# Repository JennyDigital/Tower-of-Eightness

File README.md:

# Tower-of-Eightness

Welcome to my play project of a homebrew computer based on the 6502 CPU used in many many home computers of the 80's.  This isn't meant to be a guide to how you should build a 6502 based computer but it is meant to be fun and it does work.  I had never done one before so there's lots to improve upon I'm sure and I would love to hear of any exploits or builds similar to or the same as mine.

P.S.  I am planning to bring BBC BASIC to this system as it's sooooo good.

P.P.S.  I will be continuing to develop this machine for some time especially over weekends.

Have Fun!

*JenniferDigital.*

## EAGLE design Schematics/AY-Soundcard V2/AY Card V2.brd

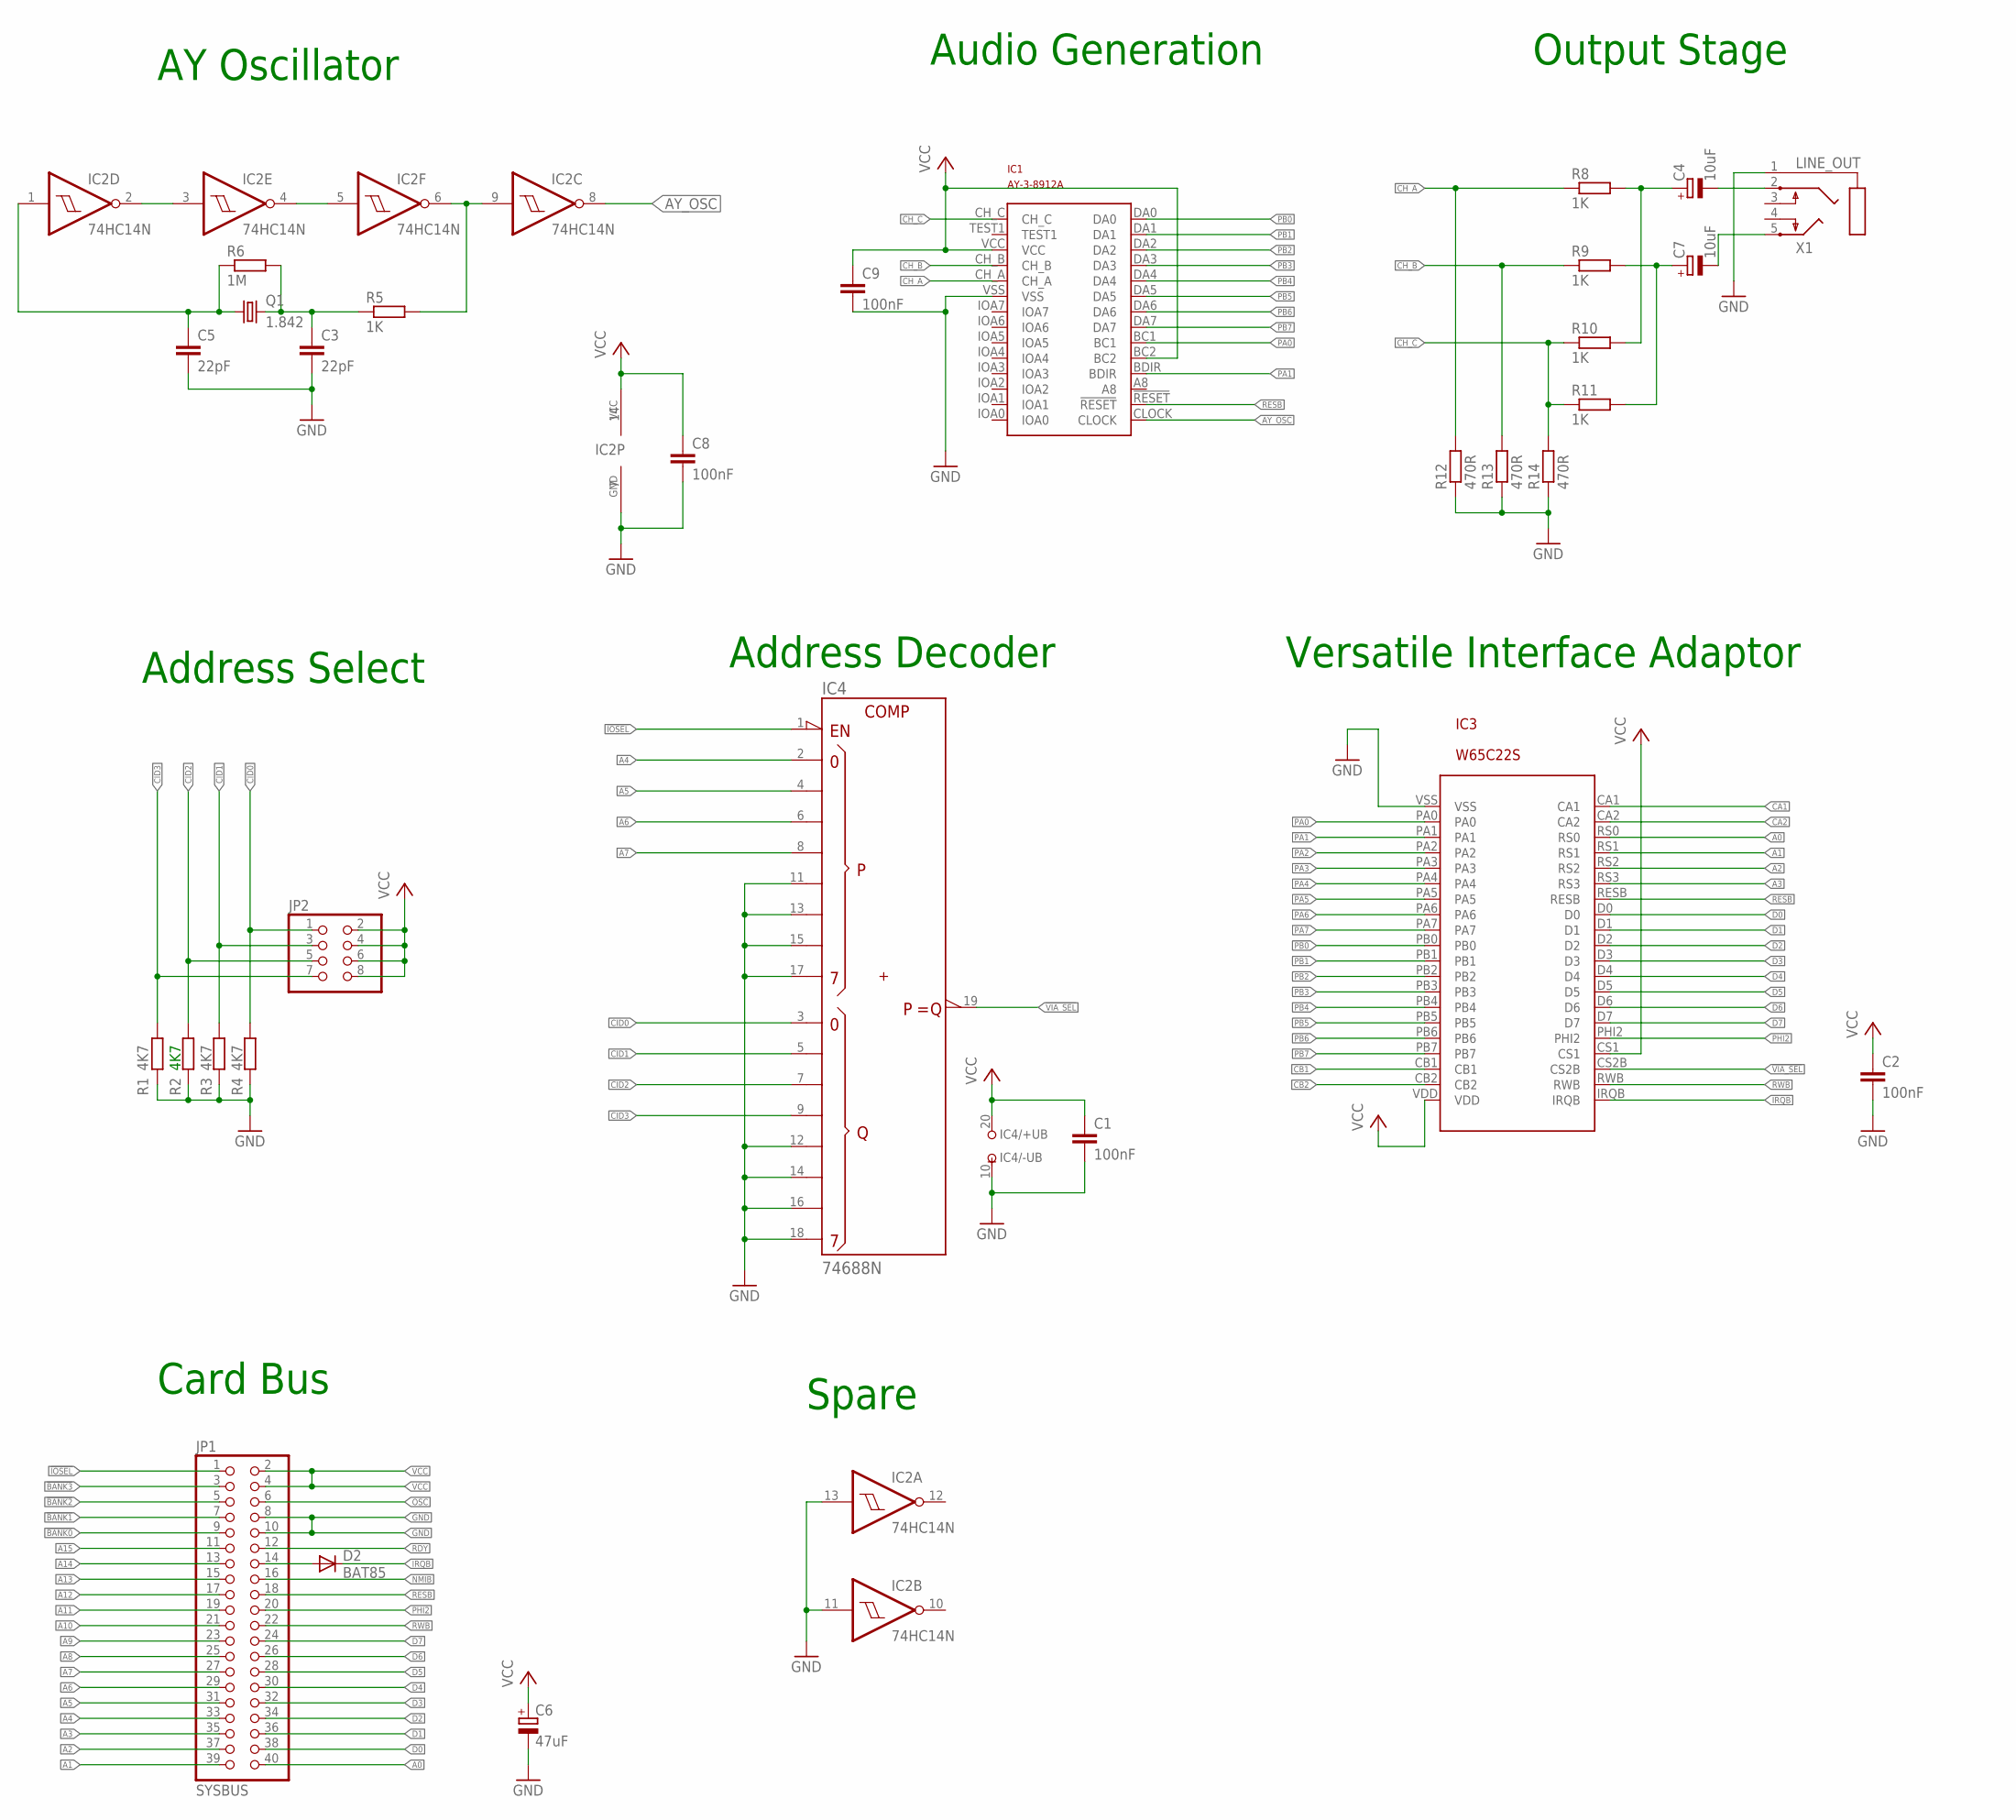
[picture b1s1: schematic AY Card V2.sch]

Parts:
C1, C2, C8, C9: 100nF; C050-025X075
C3, C5: 22pF; C050-025X075
C4, C7: 10uF; E2-5
C6: 47uF; E2,5-7
D2: BAT85; DO34-7
IC1: AY-3-8912A; DIP
IC2: 74HC14N; DIL14
IC3: W65C22S; W65C22-DIP
IC4: 74688N; DIL20
JP1: SYSBUS; 2X20/90
JP2: PINHD-2X4; 2X04
Q1: 1.842; HC49/S
R1, R2, R3, R4: 4K7; 0207/10
R5, R8, R9, R10, R11: 1K; 0207/2V
R6: 1M; 0207/2V
R12: 470R; 0207/2V
R13, R14: 470R; 0207/10
X1: LINE_OUT; STX3100

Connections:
!BANK0: JP1.9
!BANK1: JP1.7
!BANK2: JP1.5
!BANK3: JP1.3
!IOSEL: IC4.1 (!G), JP1.1
!VIA_SEL: IC3.CS2B, IC4.19 (!P=Q)
A0: IC3.RS0, JP1.40
A1: IC3.RS1, JP1.39
A2: IC3.RS2, JP1.37
A3: IC3.RS3, JP1.35
A4: IC4.2 (P0), JP1.33
A5: IC4.4 (P1), JP1.31
A6: IC4.6 (P2), JP1.29
A7: IC4.8 (P3), JP1.27
A8: JP1.25
A9: JP1.23
A10: JP1.21
A11: JP1.19
A12: JP1.17
A13: JP1.15
A14: JP1.13
A15: JP1.11
AY_OSC: IC1.CLOCK, IC2.8 (O)
CA1: IC3.CA1
CA2: IC3.CA2
CB1: IC3.CB1
CB2: IC3.CB2
CH_A: IC1.CH_A, R8.1, R12.2
CH_B: IC1.CH_B, R9.1, R13.2
CH_C: IC1.CH_C, R10.1, R11.1, R14.2
CID0: IC4.3 (Q0), JP2.1, R4.2
CID1: IC4.5 (Q1), JP2.3, R3.2
CID2: IC4.7 (Q2), JP2.5, R2.2
CID3: IC4.9 (Q3), JP2.7, R1.2
D0: IC3.D0, JP1.38
D1: IC3.D1, JP1.36
D2: IC3.D2, JP1.34
D3: IC3.D3, JP1.32
D4: IC3.D4, JP1.30
D5: IC3.D5, JP1.28
D6: IC3.D6, JP1.26
D7: IC3.D7, JP1.24
GND: C1.2, C2.2, C3.2, C5.2, C6.-, C8.2, C9.2, IC1.VSS, IC2.7 (GND), IC2.11 (I), IC2.13 (I), IC3.VSS, IC4.10 (-UB), IC4.11 (P4), IC4.12 (Q4), IC4.13 (P5), IC4.14 (Q5), IC4.15 (P6), IC4.16 (Q6), IC4.17 (P7), IC4.18 (Q7), JP1.8, JP1.10, R1.1, R2.1, R3.1, R4.1, R12.1, R13.1, R14.1, X1.1
IRQB: D2.C, IC3.IRQB
unnamed: D2.A, JP1.14
unnamed: C4.+, R8.2, R10.2
unnamed: C7.+, R9.2, R11.2
unnamed: C7.-, X1.5
unnamed: C4.-, X1.2
unnamed: IC2.4 (O), IC2.5 (I)
unnamed: IC2.6 (O), IC2.9 (I), R5.2
unnamed: C3.1, Q1.2, R5.1, R6.2
unnamed: C5.1, IC2.1 (I), Q1.1, R6.1
unnamed: IC2.2 (O), IC2.3 (I)
NMIB: JP1.16
OSC: JP1.6
PA0: IC1.BC1, IC3.PA0
PA1: IC1.BDIR, IC3.PA1
PA2: IC3.PA2
PA3: IC3.PA3
PA4: IC3.PA4
PA5: IC3.PA5
PA6: IC3.PA6
PA7: IC3.PA7
PB0: IC1.DA0, IC3.PB0
PB1: IC1.DA1, IC3.PB1
PB2: IC1.DA2, IC3.PB2
PB3: IC1.DA3, IC3.PB3
PB4: IC1.DA4, IC3.PB4
PB5: IC1.DA5, IC3.PB5
PB6: IC1.DA6, IC3.PB6
PB7: IC1.DA7, IC3.PB7
PHI2: IC3.PHI2, JP1.20
RDY: JP1.12
RESB: IC1.!RESET, IC3.RESB, JP1.18
RWB: IC3.RWB, JP1.22
VCC: C1.1, C2.1, C6.+, C8.1, C9.1, IC1.BC2, IC1.VCC, IC2.14 (VCC), IC3.CS1, IC3.VDD, IC4.20 (+UB), JP1.2, JP1.4, JP2.2, JP2.4, JP2.6, JP2.8

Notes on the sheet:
Card Bus
Address Select
Address Decoder
Versatile Interface Adaptor
Audio Generation
Output Stage
AY Oscillator
Spare

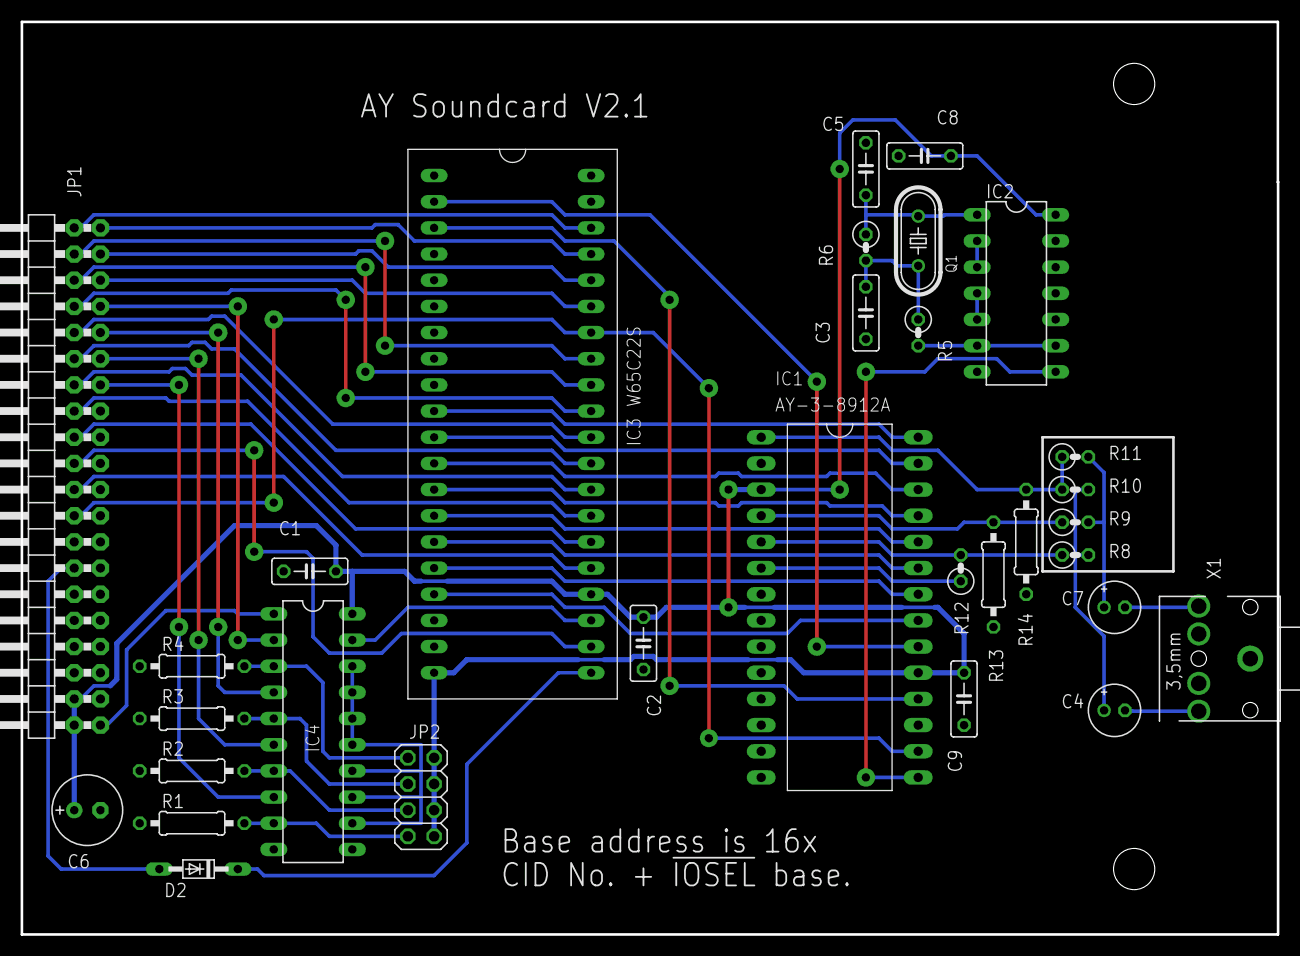
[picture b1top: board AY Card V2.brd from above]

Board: 2 copper layers, 121.9 x 88.6 mm, 31 parts (0 on the bottom side), 52 nets.

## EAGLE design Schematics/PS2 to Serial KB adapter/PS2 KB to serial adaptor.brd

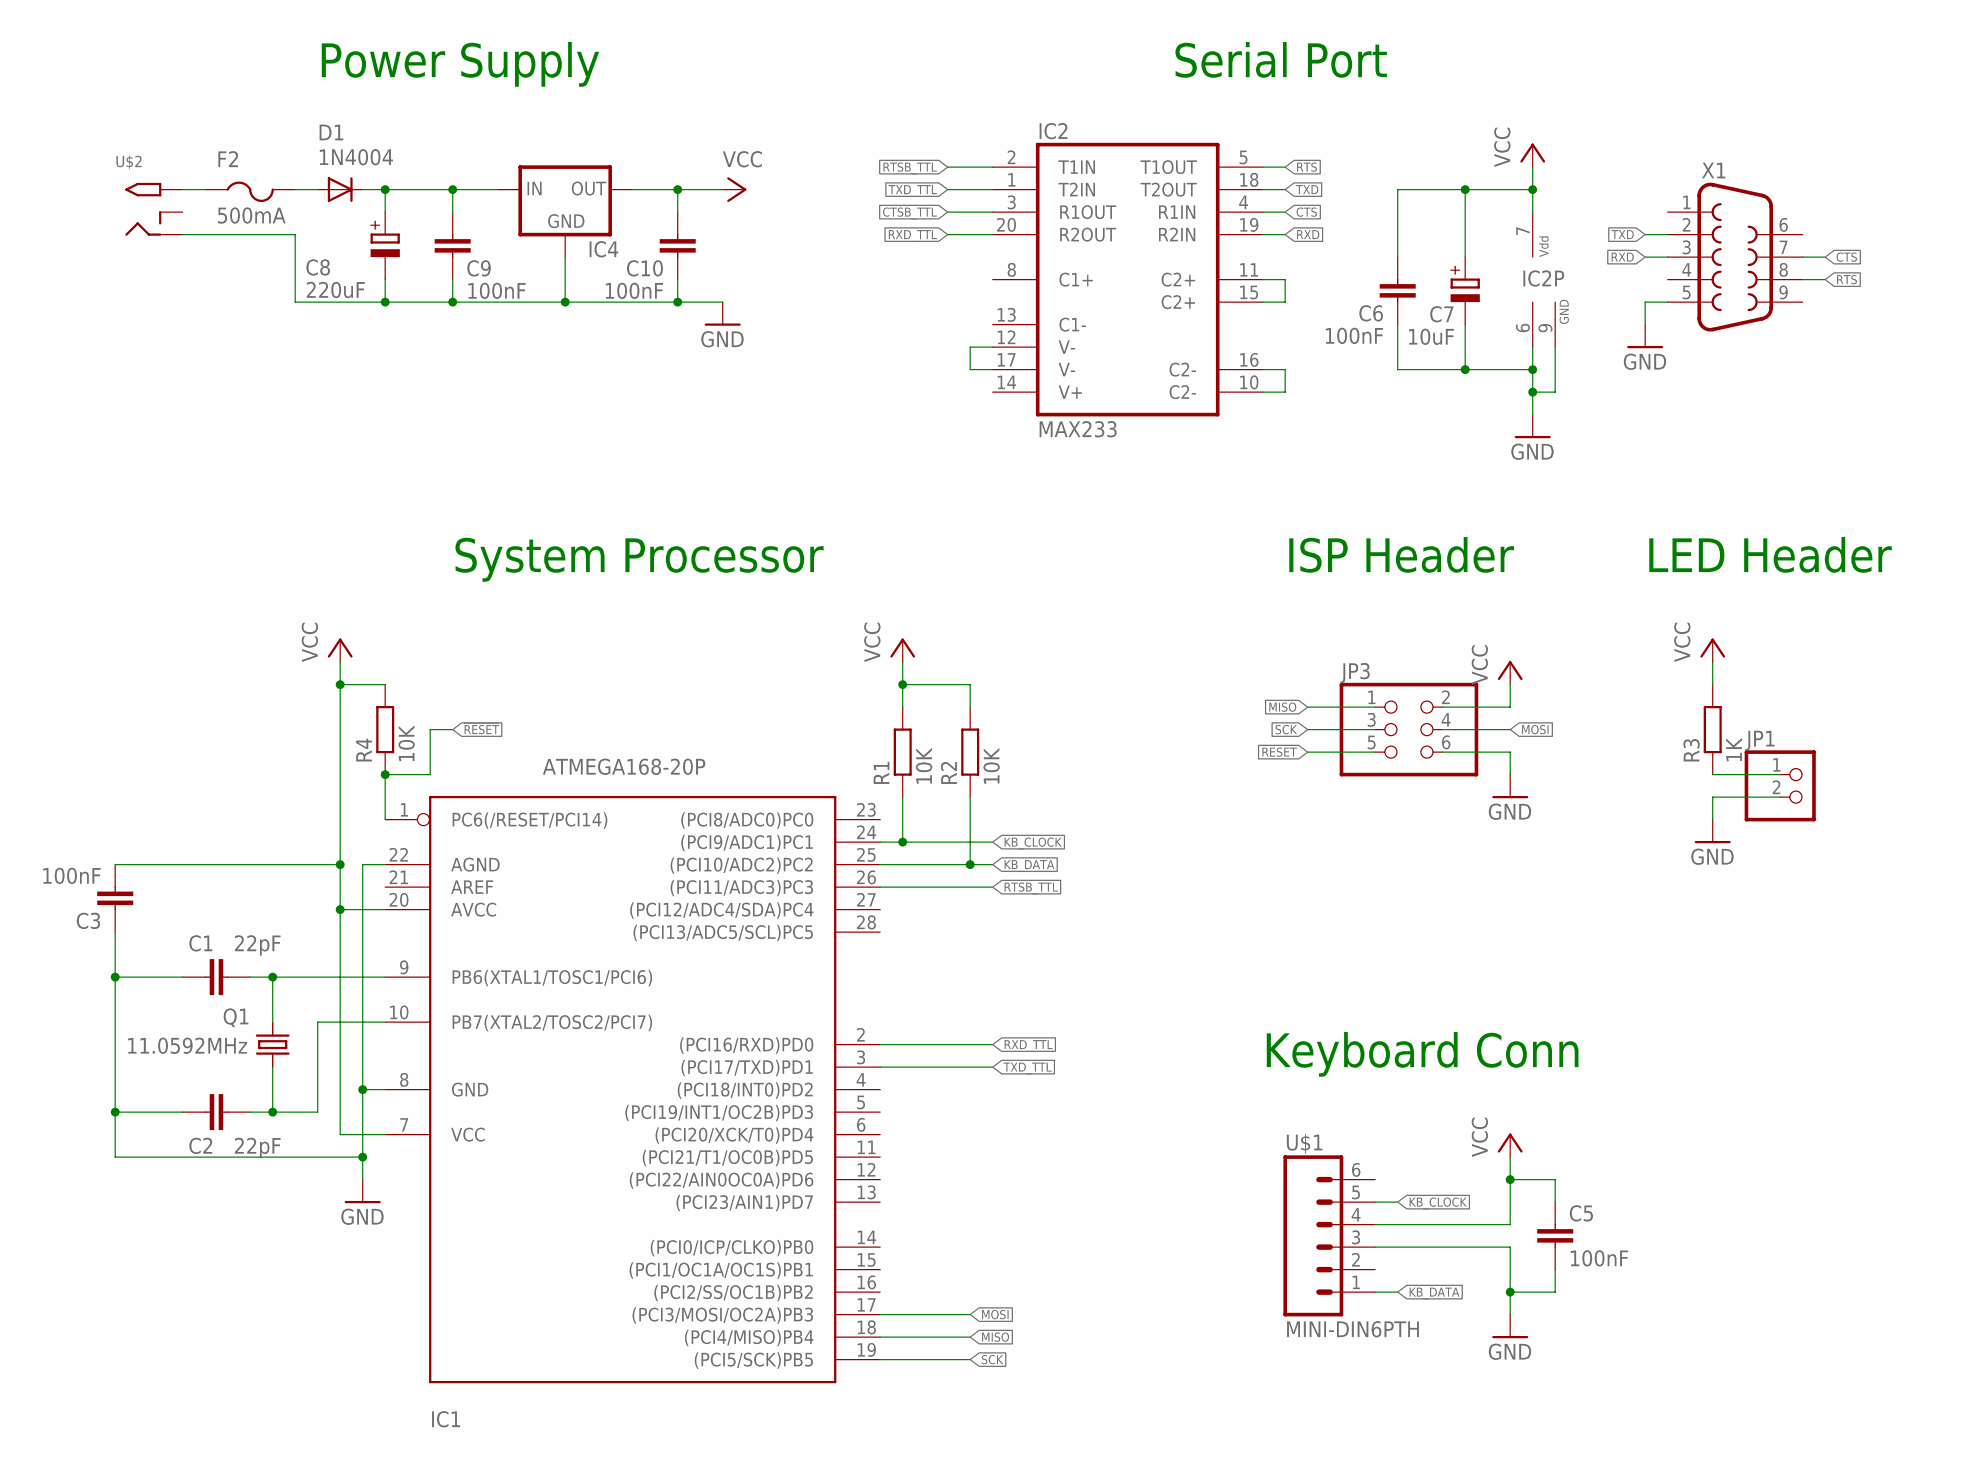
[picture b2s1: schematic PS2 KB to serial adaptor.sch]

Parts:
C1, C2: 22pF; C025-024X044
C3, C6, C9, C10: 100nF; C025-024X044
C5: 100nF; C050-024X044
C7: 10uF; E2,5-5
C8: 220uF; E2,5-7
D1: 1N4004; DO41-10
F2: 500mA; 1812
IC1: ATMEGA168-20P; DIL28-3
IC2: MAX233; DIL20
IC4: 78XXL
JP1: PINHD-1X2; 1X02
JP3: PINHD-2X3; 2X03
Q1: 11.0592MHz; HC49U-V
R1, R2: 10K; 0207/2V
R3: 1K; 0207/2V
R4: 10K; 0207/7
U$1: MINI-DIN6PTH; MINI-DIN6
U$2: 2.1MMJACKTHM; PJ-102A
X1: F09HP

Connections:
!RESET: IC1.1 (PC6(/RESET/PCI14)), JP3.5, R4.1
CTS: IC2.4 (R1IN), X1.7
CTSB_TTL: IC2.3 (R1OUT)
GND: C1.1, C2.1, C3.1, C5.1, C6.1, C7.-, C8.-, C9.1, C10.1, IC1.8 (GND), IC1.22 (AGND), IC2.6 (GND), IC2.9 (GND), IC4.GND, JP1.2, JP3.6, U$1.3, U$2.RING, X1.5
KB_CLOCK: IC1.24 ((PCI9/ADC1)PC1), R1.1, U$1.5
KB_DATA: IC1.25 ((PCI10/ADC2)PC2), R2.1, U$1.1
MISO: IC1.18 ((PCI4/MISO)PB4), JP3.1
MOSI: IC1.17 ((PCI3/MOSI/OC2A)PB3), JP3.4
unnamed: IC2.12 (V-), IC2.17 (V-)
unnamed: IC2.11 (C2+), IC2.15 (C2+)
unnamed: IC2.10 (C2-), IC2.16 (C2-)
unnamed: C8.+, C9.2, D1.C, IC4.IN
unnamed: JP1.1, R3.1
unnamed: D1.A, F2.2
unnamed: C1.2, IC1.9 (PB6(XTAL1/TOSC1/PCI6)), Q1.2
unnamed: C2.2, IC1.10 (PB7(XTAL2/TOSC2/PCI7)), Q1.1
unnamed: F2.1, U$2.TIP
RTS: IC2.5 (T1OUT), X1.8
RTSB_TTL: IC1.26 ((PCI11/ADC3)PC3), IC2.2 (T1IN)
RXD: IC2.19 (R2IN), X1.3
RXD_TTL: IC1.2 ((PCI16/RXD)PD0), IC2.20 (R2OUT)
SCK: IC1.19 ((PCI5/SCK)PB5), JP3.3
TXD: IC2.18 (T2OUT), X1.2
TXD_TTL: IC1.3 ((PCI17/TXD)PD1), IC2.1 (T2IN)
VCC: C3.2, C5.2, C6.2, C7.+, C10.2, IC1.7 (VCC), IC1.20 (AVCC), IC2.7 (VDD), IC4.OUT, JP3.2, R1.2, R2.2, R3.2, R4.2, U$1.4

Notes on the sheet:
Power Supply
Keyboard Conn
Serial Port
System Processor
ISP Header
LED Header

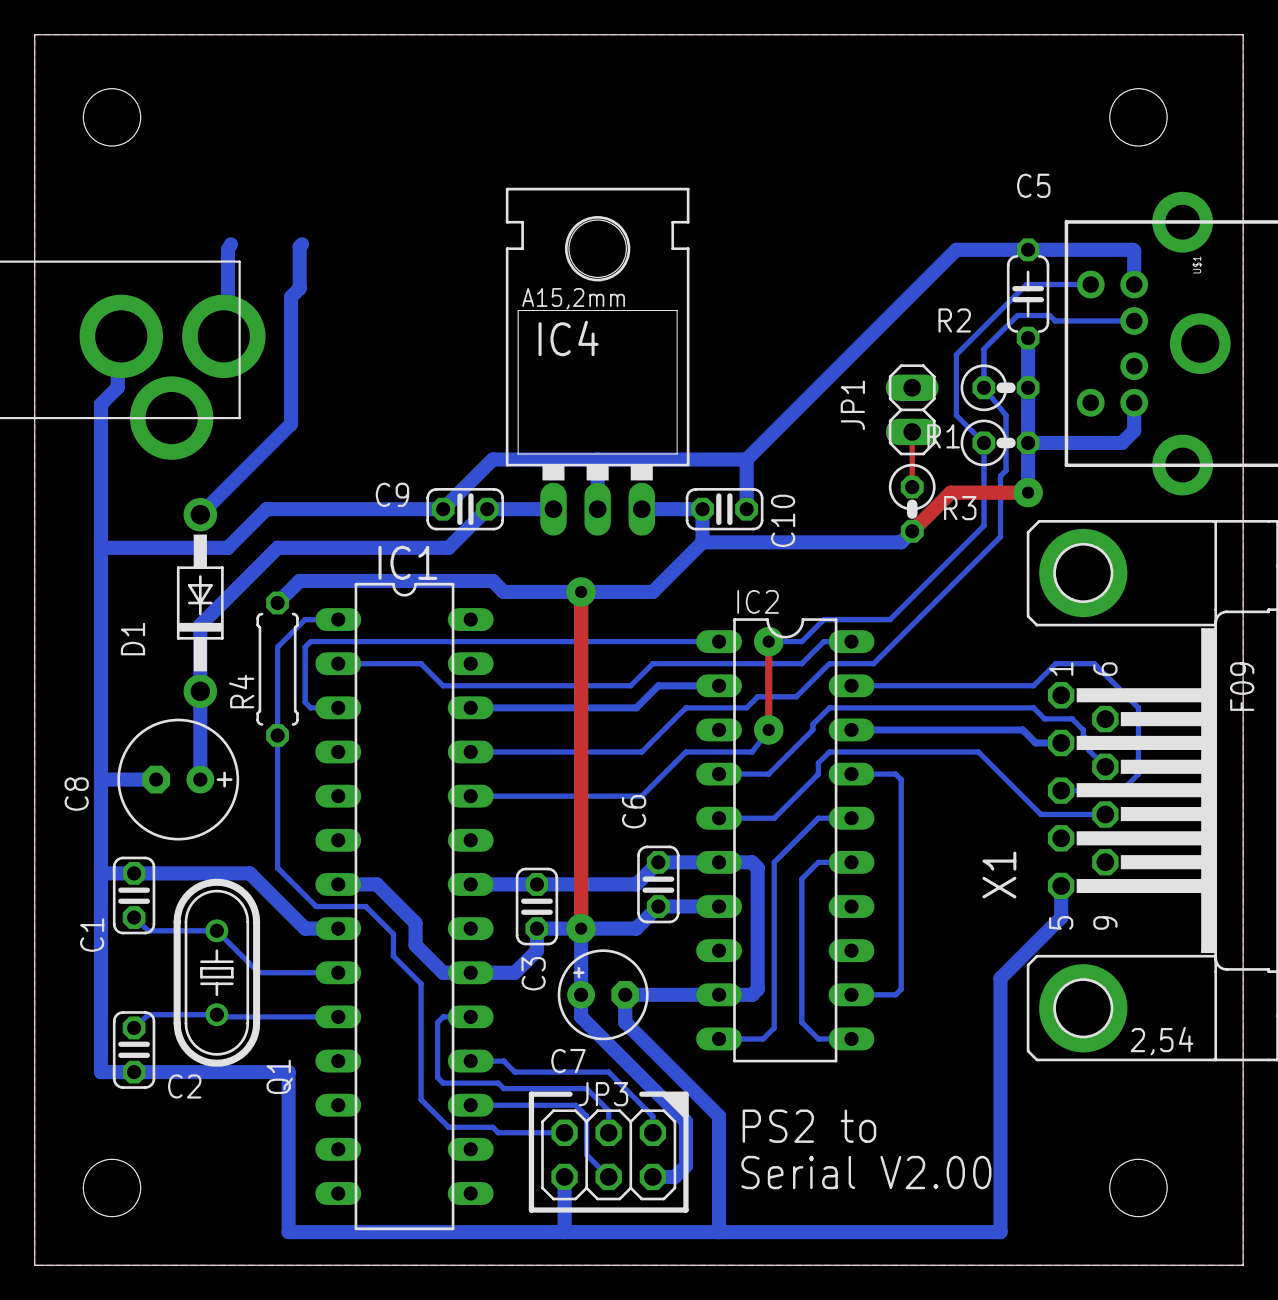
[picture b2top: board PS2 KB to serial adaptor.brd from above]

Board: 2 copper layers, 69.5 x 70.8 mm, 24 parts (1 on the bottom side), 24 nets.

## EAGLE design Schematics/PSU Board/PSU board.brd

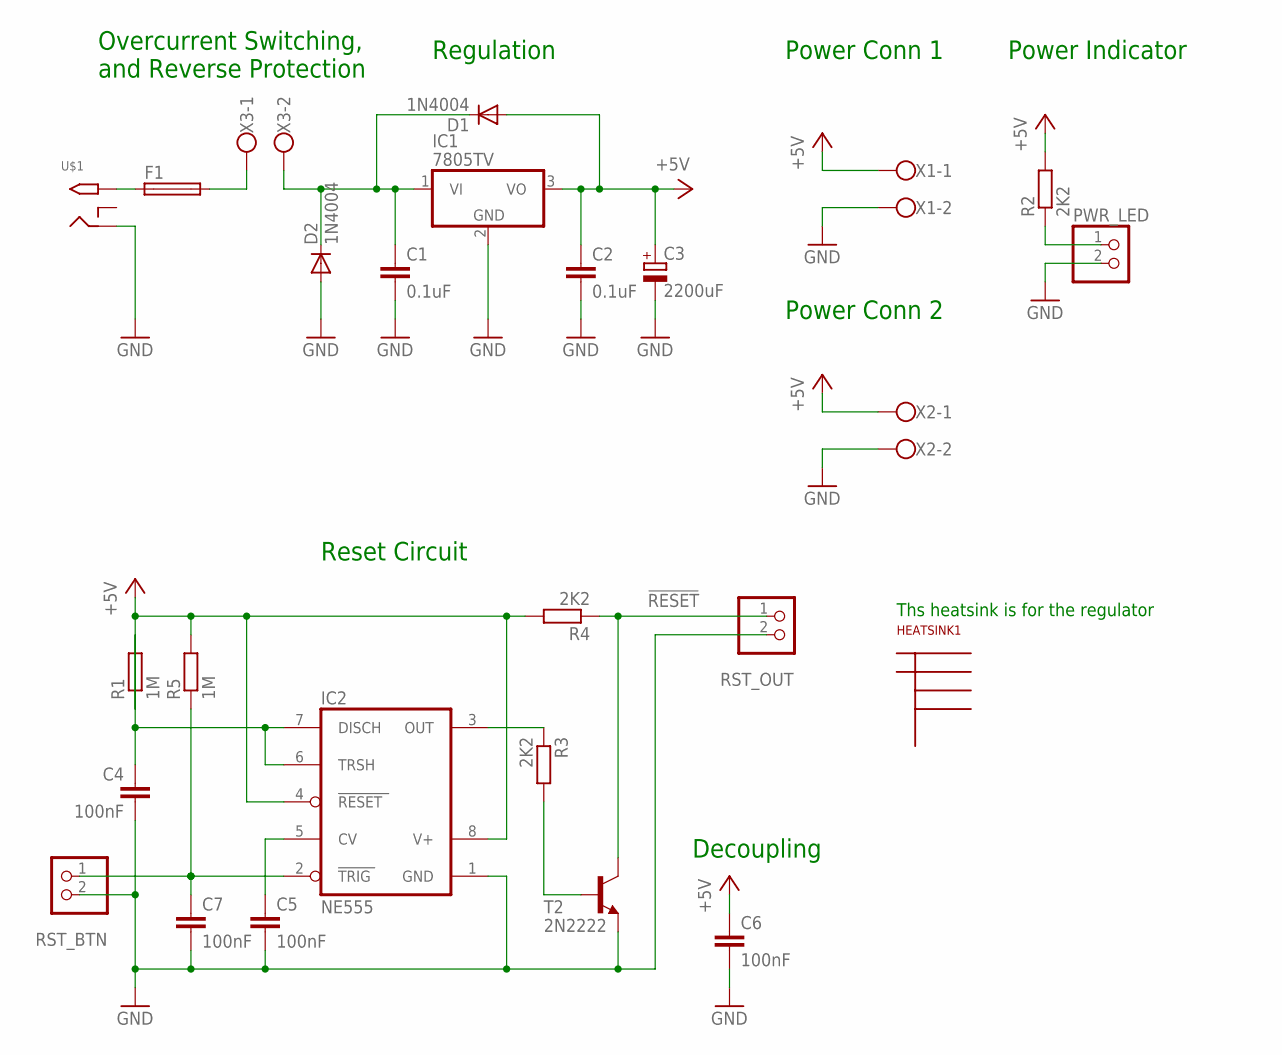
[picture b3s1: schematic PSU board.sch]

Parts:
C1, C2: 0.1uF; C025-025X050
C3: 2200uF; E7,5-18
C4, C5, C6, C7: 100nF; C025-025X050
D1, D2: 1N4004; DO41-10
F1: SH22,5A
HEATSINK1: FISCHER-50_HSINK; FISHER-50
IC1: 7805TV; TO220V
IC2: NE555; DIL08
PWR_LED: PINHD-1X2; 1X02
R1: 1M; 0207/2V
R2: 2K2; 0207/10
R3, R4: 2K2; 0207/2V
R5: 1M; 0207/10
RST_BTN: PINHD-1X2; 1X02
RST_OUT: PINHD-1X2; 1X02
T2: 2N2222; TO18
U$1: 2.1MMJACKTHM; PJ-102A
X1, X2, X3: W237-102

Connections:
!RESET: R4.1, RST_OUT.1, T2.3 (C)
+5V: C2.1, C3.+, C6.1, D1.A, IC1.3 (VO), IC2.4 (RESET), IC2.8 (V+), R1.1, R2.2, R4.2, R5.2, X1.1, X2.1
+V_IN: C1.1, D1.C, D2.C, IC1.1 (VI), X3.2
GND: C1.2, C2.2, C3.-, C4.2, C5.2, C6.2, C7.2, D2.A, IC1.2 (GND), IC2.1 (GND), PWR_LED.2, RST_BTN.2, RST_OUT.2, T2.1 (E), U$1.RING, X1.2, X2.2
unnamed: PWR_LED.1, R2.1
unnamed: F1.2, X3.1
unnamed: F1.1, U$1.TIP
unnamed: C4.1, IC2.6 (TRSH), IC2.7 (DISCH), R1.2
unnamed: C5.1, IC2.5 (CV)
unnamed: C7.1, IC2.2 (TRIG), R5.1, RST_BTN.1
unnamed: R3.2, T2.2 (B)
unnamed: IC2.3 (OUT), R3.1

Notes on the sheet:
Decoupling
Regulation
Overcurrent Switching, and Reverse Protection
Power Indicator
Reset Circuit
Power Conn 1
Power Conn 2
Ths heatsink is for the regulator

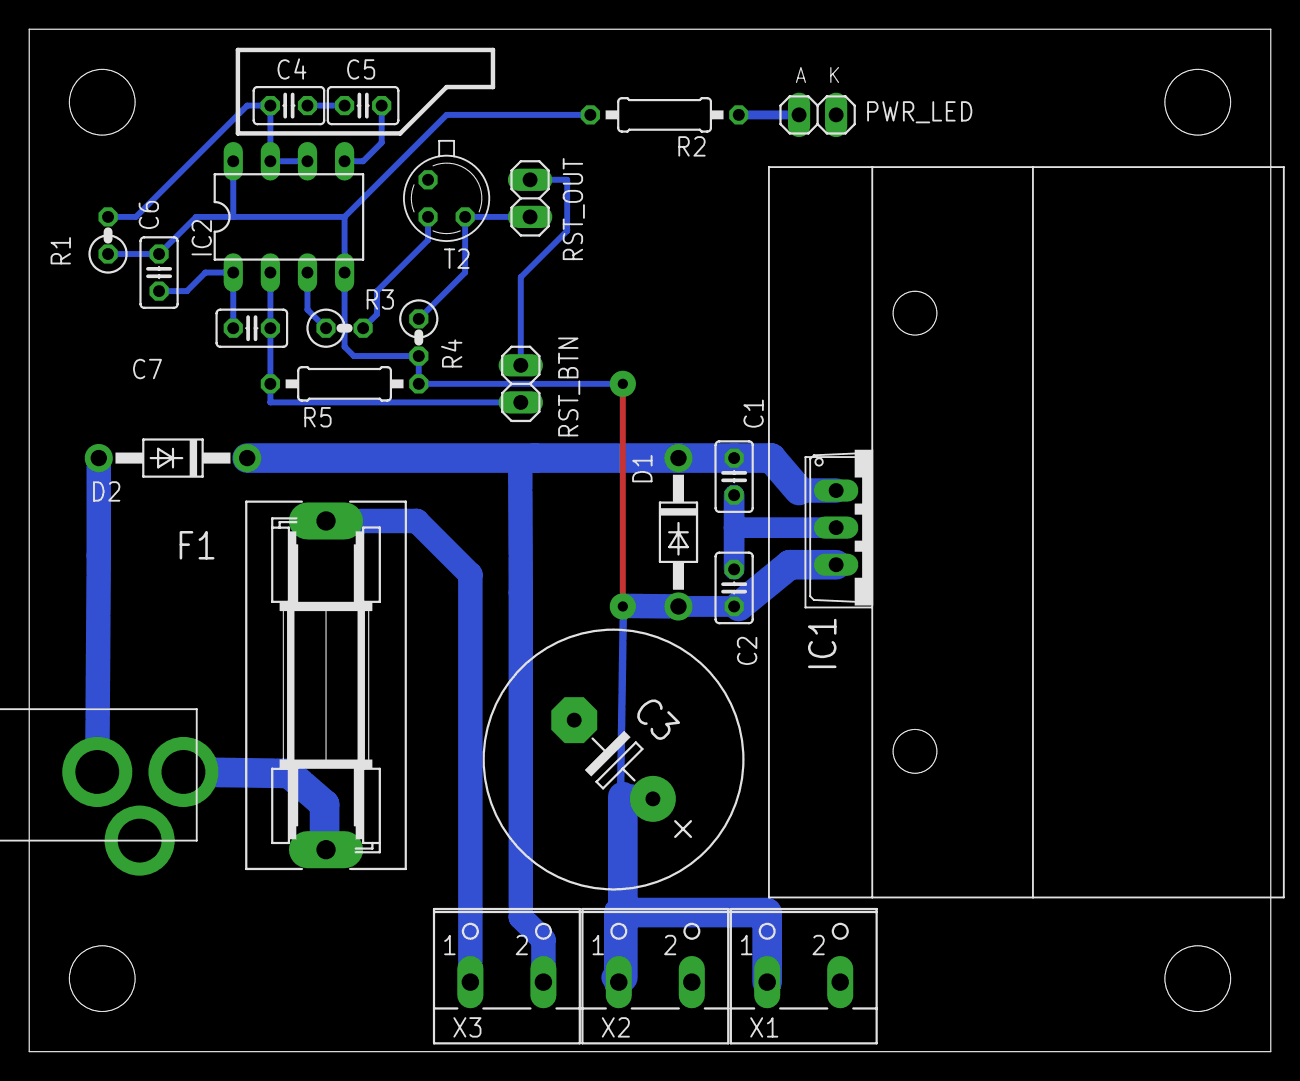
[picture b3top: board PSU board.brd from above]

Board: 2 copper layers, 85.0 x 70.0 mm, 26 parts (0 on the bottom side), 12 nets.

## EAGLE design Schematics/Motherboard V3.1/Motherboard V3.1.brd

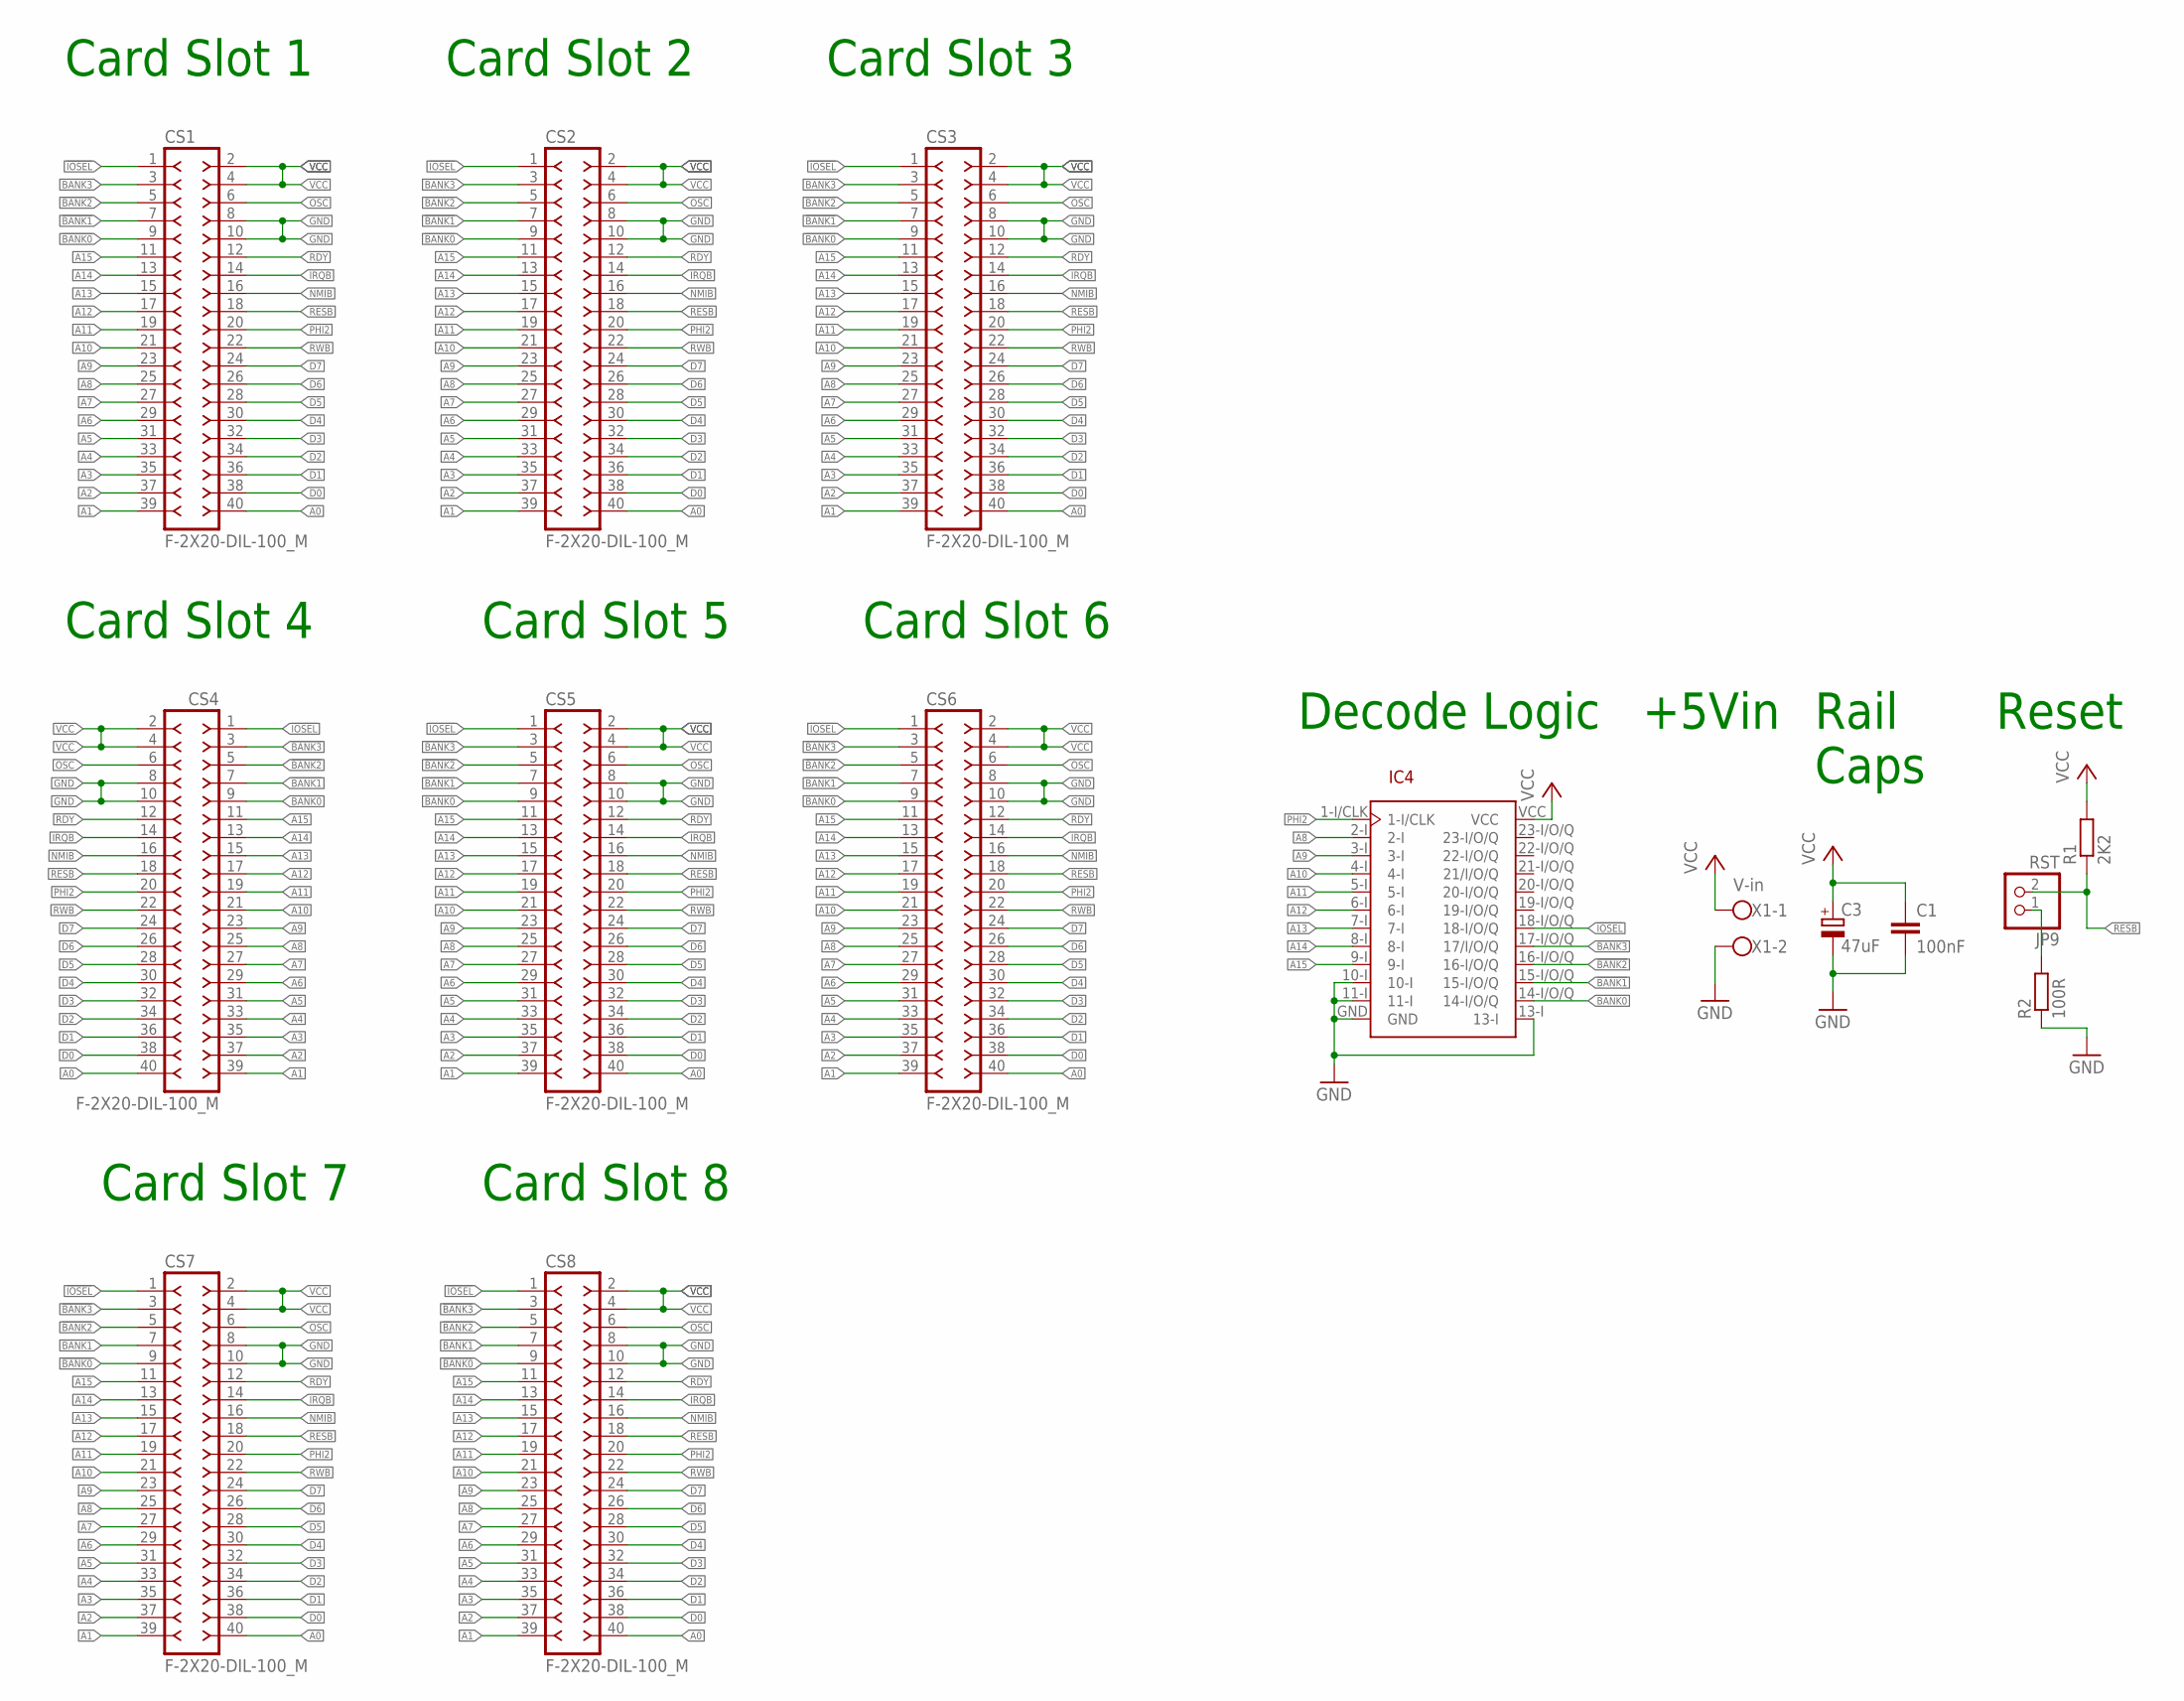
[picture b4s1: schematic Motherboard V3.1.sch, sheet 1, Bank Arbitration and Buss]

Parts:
C1: 100nF; C050-025X075
C3: 47uF; E2,5-7
CS1, CS2, CS3, CS4, CS5, CS6, CS7, CS8: F-2X20-DIL-100_M; DIL-100-2X20_M
IC4: GAL22V10D-7LP; DIP24
JP9: RST; 1X02
R1: 2K2; 0207/10
R2: 100R; 0207/10
X1: V-in; W237-102

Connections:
!BANK0: CS1.9, CS2.9, CS3.9, CS4.9, CS5.9, CS6.9, CS7.9, CS8.9, IC4.14-I/O/Q
!BANK1: CS1.7, CS2.7, CS3.7, CS4.7, CS5.7, CS6.7, CS7.7, CS8.7, IC4.15-I/O/Q
!BANK2: CS1.5, CS2.5, CS3.5, CS4.5, CS5.5, CS6.5, CS7.5, CS8.5, IC4.16-I/O/Q
!BANK3: CS1.3, CS2.3, CS3.3, CS4.3, CS5.3, CS6.3, CS7.3, CS8.3, IC4.17-I/O/Q (17/I/O/Q)
!IOSEL: CS1.1, CS2.1, CS3.1, CS4.1, CS5.1, CS6.1, CS7.1, CS8.1, IC4.18-I/O/Q
A0: CS1.40, CS2.40, CS3.40, CS4.40, CS5.40, CS6.40, CS7.40, CS8.40; also elsewhere on the board
A1: CS1.39, CS2.39, CS3.39, CS4.39, CS5.39, CS6.39, CS7.39, CS8.39; also elsewhere on the board
A2: CS1.37, CS2.37, CS3.37, CS4.37, CS5.37, CS6.37, CS7.37, CS8.37; also elsewhere on the board
A3: CS1.35, CS2.35, CS3.35, CS4.35, CS5.35, CS6.35, CS7.35, CS8.35; also elsewhere on the board
A4: CS1.33, CS2.33, CS3.33, CS4.33, CS5.33, CS6.33, CS7.33, CS8.33; also elsewhere on the board
A5: CS1.31, CS2.31, CS3.31, CS4.31, CS5.31, CS6.31, CS7.31, CS8.31; also elsewhere on the board
A6: CS1.29, CS2.29, CS3.29, CS4.29, CS5.29, CS6.29, CS7.29, CS8.29; also elsewhere on the board
A7: CS1.27, CS2.27, CS3.27, CS4.27, CS5.27, CS6.27, CS7.27, CS8.27; also elsewhere on the board
A8: CS1.25, CS2.25, CS3.25, CS4.25, CS5.25, CS6.25, CS7.25, CS8.25, IC4.2-I; also elsewhere on the board
A9: CS1.23, CS2.23, CS3.23, CS4.23, CS5.23, CS6.23, CS7.23, CS8.23, IC4.3-I; also elsewhere on the board
A10: CS1.21, CS2.21, CS3.21, CS4.21, CS5.21, CS6.21, CS7.21, CS8.21, IC4.4-I; also elsewhere on the board
A11: CS1.19, CS2.19, CS3.19, CS4.19, CS5.19, CS6.19, CS7.19, CS8.19, IC4.5-I; also elsewhere on the board
A12: CS1.17, CS2.17, CS3.17, CS4.17, CS5.17, CS6.17, CS7.17, CS8.17, IC4.6-I; also elsewhere on the board
A13: CS1.15, CS2.15, CS3.15, CS4.15, CS5.15, CS6.15, CS7.15, CS8.15, IC4.7-I; also elsewhere on the board
A14: CS1.13, CS2.13, CS3.13, CS4.13, CS5.13, CS6.13, CS7.13, CS8.13, IC4.8-I; also elsewhere on the board
A15: CS1.11, CS2.11, CS3.11, CS4.11, CS5.11, CS6.11, CS7.11, CS8.11, IC4.9-I; also elsewhere on the board
D0: CS1.38, CS2.38, CS3.38, CS4.38, CS5.38, CS6.38, CS7.38, CS8.38; also elsewhere on the board
D1: CS1.36, CS2.36, CS3.36, CS4.36, CS5.36, CS6.36, CS7.36, CS8.36; also elsewhere on the board
D2: CS1.34, CS2.34, CS3.34, CS4.34, CS5.34, CS6.34, CS7.34, CS8.34; also elsewhere on the board
D3: CS1.32, CS2.32, CS3.32, CS4.32, CS5.32, CS6.32, CS7.32, CS8.32; also elsewhere on the board
D4: CS1.30, CS2.30, CS3.30, CS4.30, CS5.30, CS6.30, CS7.30, CS8.30; also elsewhere on the board
D5: CS1.28, CS2.28, CS3.28, CS4.28, CS5.28, CS6.28, CS7.28, CS8.28; also elsewhere on the board
D6: CS1.26, CS2.26, CS3.26, CS4.26, CS5.26, CS6.26, CS7.26, CS8.26; also elsewhere on the board
D7: CS1.24, CS2.24, CS3.24, CS4.24, CS5.24, CS6.24, CS7.24, CS8.24; also elsewhere on the board
GND: C1.2, C3.-, CS1.8, CS1.10, CS2.8, CS2.10, CS3.8, CS3.10, CS4.8, CS4.10, CS5.8, CS5.10, CS6.8, CS6.10, CS7.8, CS7.10, CS8.8, CS8.10, IC4.10-I, IC4.11-I, IC4.13-I, IC4.GND, R2.1, X1.2; also elsewhere on the board
IRQB: CS1.14, CS2.14, CS3.14, CS4.14, CS5.14, CS6.14, CS7.14, CS8.14; also elsewhere on the board
unnamed: JP9.1, R2.2
NMIB: CS1.16, CS2.16, CS3.16, CS4.16, CS5.16, CS6.16, CS7.16, CS8.16; also elsewhere on the board
OSC: CS1.6, CS2.6, CS3.6, CS4.6, CS5.6, CS6.6, CS7.6, CS8.6; also elsewhere on the board
PHI2: CS1.20, CS2.20, CS3.20, CS4.20, CS5.20, CS6.20, CS7.20, CS8.20, IC4.1-I/CLK; also elsewhere on the board
RDY: CS1.12, CS2.12, CS3.12, CS4.12, CS5.12, CS6.12, CS7.12, CS8.12; also elsewhere on the board
RESB: CS1.18, CS2.18, CS3.18, CS4.18, CS5.18, CS6.18, CS7.18, CS8.18, JP9.2, R1.1; also elsewhere on the board
RWB: CS1.22, CS2.22, CS3.22, CS4.22, CS5.22, CS6.22, CS7.22, CS8.22; also elsewhere on the board
VCC: C1.1, C3.+, CS1.2, CS1.4, CS2.2, CS2.4, CS3.2, CS3.4, CS4.2, CS4.4, CS5.2, CS5.4, CS6.2, CS6.4, CS7.2, CS7.4, CS8.2, CS8.4, IC4.VCC, R1.2, X1.1; also elsewhere on the board

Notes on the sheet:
Decode Logic
Card Slot 1
Card Slot 2
Card Slot 3
Card Slot 4
Reset
+5Vin
Rail Caps
Card Slot 5
Card Slot 6
Card Slot 7
Card Slot 8

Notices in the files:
parts and their libraries:
SparkFun-DigitalIC: Licensing: CC v3.0 Share-Alike You are welcome to use this library for commercial purposes.
con-headers-jp: Copyright (C) 2008, Bob Starr
